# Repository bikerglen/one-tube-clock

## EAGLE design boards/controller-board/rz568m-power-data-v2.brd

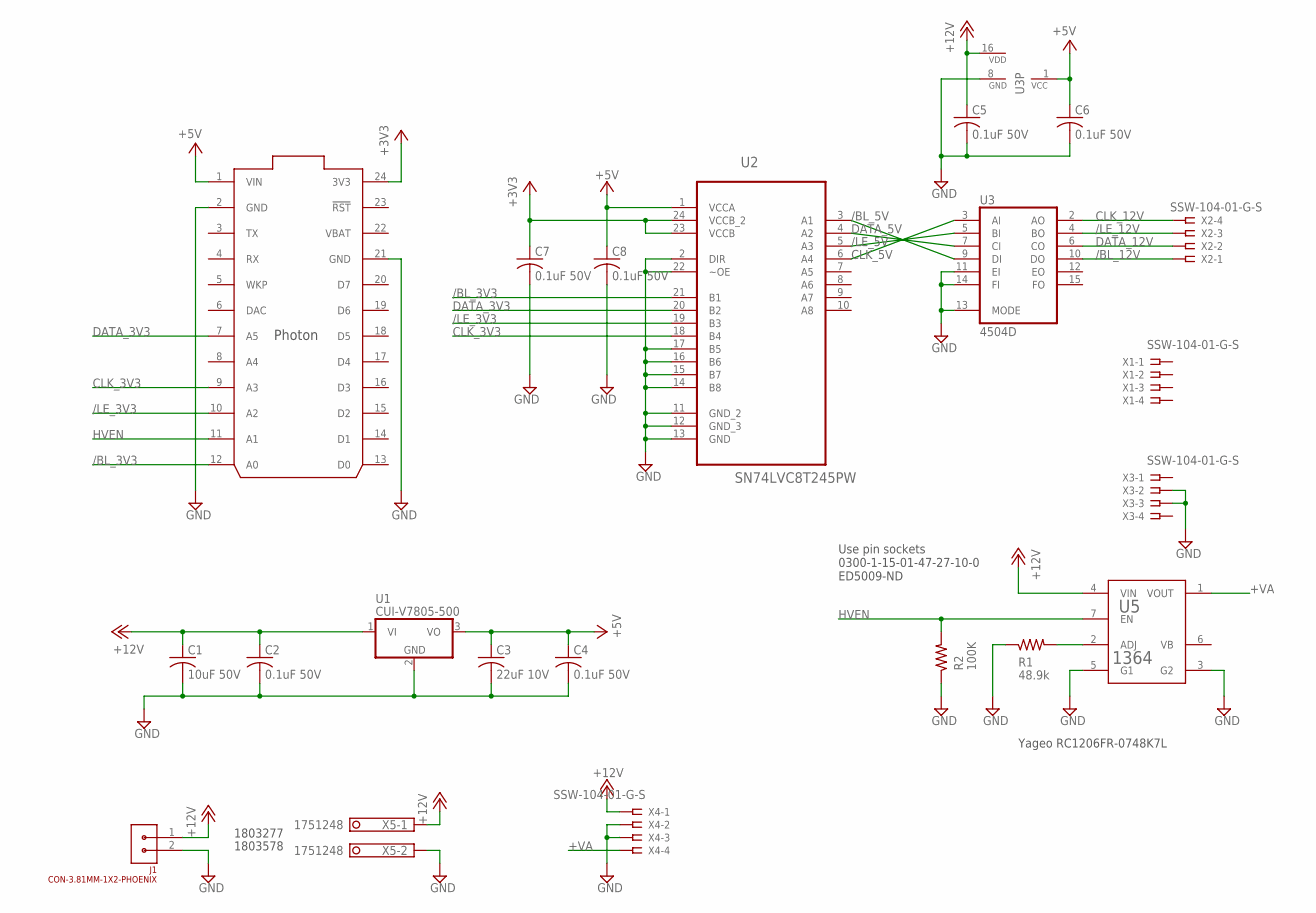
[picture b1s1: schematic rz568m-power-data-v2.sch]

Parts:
C1: 10uF 50V; C1210K; MFR_PART_NO C1210C106K5RACTU
C2, C4: 0.1uF 50V; C1206K; MFR_PART_NO C1206S104M5RACTU
C3: 22uF 10V; C1206K; MFR_PART_NO C1206C226K8RAC7800
C5, C6, C7, C8: 0.1uF 50V; C0805K; MFR_PART_NO C1206S104M5RACTU
J1: CON-3.81MM-1X2-PHOENIX; CON-PHOENIX-3.81-1X2-RA
R1: 48.9k; R1206
R2: 100K; R1206
U1: CUI-V7805-500; CUI-78XX-500
U2: SN74LVC8T245PW; SOP65P640X120-24N
U3: 4504D; SO16
U4: PHOTON_WITH_HEADERS; PHOTON
U5: 1364
X1, X2, X3, X4: SSW-104-01-G-S; SSW-104-02-S-S
X5: 1751248

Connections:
+3V3: C7.1, U2.23 (VCCB), U2.24 (VCCB_2), U4.24 (3V3)
+5V: C3.1, C4.1, C6.1, C8.1, U1.3 (VO), U2.1 (VCCA), U3.1 (VCC), U4.1 (VIN)
+12V: C1.1, C2.1, C5.1, J1.1, U1.1 (VI), U3.16 (VDD), U5.4 (VIN), X4.1, X5.1
+VA: U5.1 (VOUT), X4.4
/BL_3V3: U2.21 (B1), U4.12 (A0)
/BL_5V: U2.3 (A1), U3.9 (DI)
/BL_12V: U3.10 (DO), X2.1
/LE_3V3: U2.19 (B3), U4.10 (A2)
/LE_5V: U2.5 (A3), U3.5 (BI)
/LE_12V: U3.4 (BO), X2.3
CLK_3V3: U2.18 (B4), U4.9 (A3)
CLK_5V: U2.6 (A4), U3.3 (AI)
CLK_12V: U3.2 (AO), X2.4
DATA_3V3: U2.20 (B2), U4.7 (A5)
DATA_5V: U2.4 (A2), U3.7 (CI)
DATA_12V: U3.6 (CO), X2.2
GND: C1.2, C2.2, C3.2, C4.2, C5.2, C6.2, C7.2, C8.2, J1.2, R1.1, R2.1, U1.2 (GND), U2.2 (DIR), U2.11 (GND_2), U2.12 (GND_3), U2.13 (GND), U2.14 (B8), U2.15 (B7), U2.16 (B6), U2.17 (B5), U2.22 (~OE), U3.8 (GND), U3.11 (EI), U3.13 (MODE), U3.14 (FI), U4.2 (GND), U4.21 (GND), U5.3 (G2), U5.5 (G1), X3.2, X3.3, X4.2, X4.3, X5.2
HVEN: R2.2, U4.11 (A1), U5.7 (EN)
unnamed: R1.2, U5.2 (ADJ)
VBAT: U4.22 (VBAT)

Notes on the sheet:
Yageo RC1206FR-0748K7L
1803277
1803578
Use pin sockets 0300-1-15-01-47-27-10-0 ED5009-ND

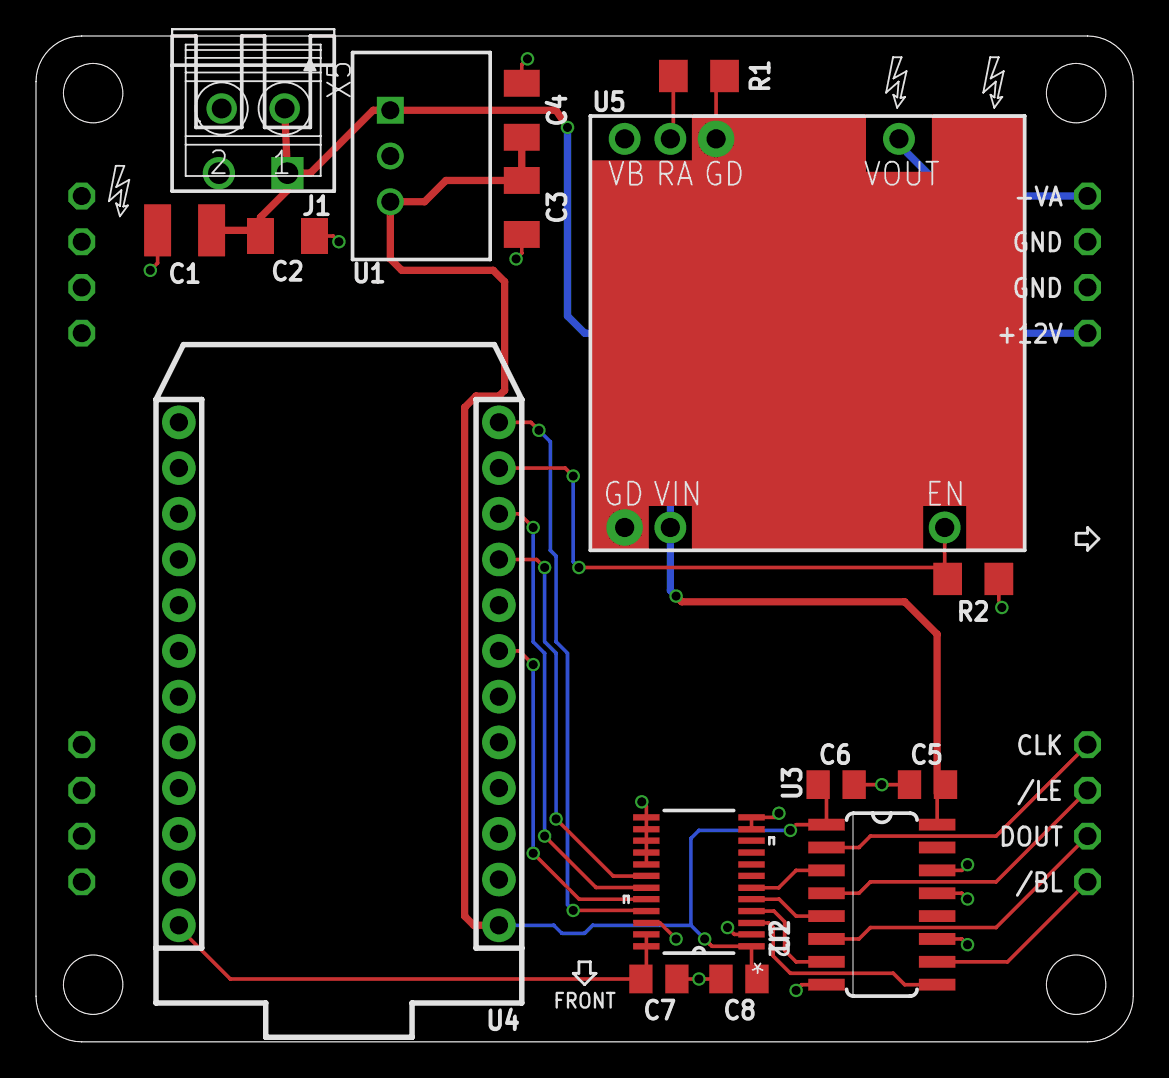
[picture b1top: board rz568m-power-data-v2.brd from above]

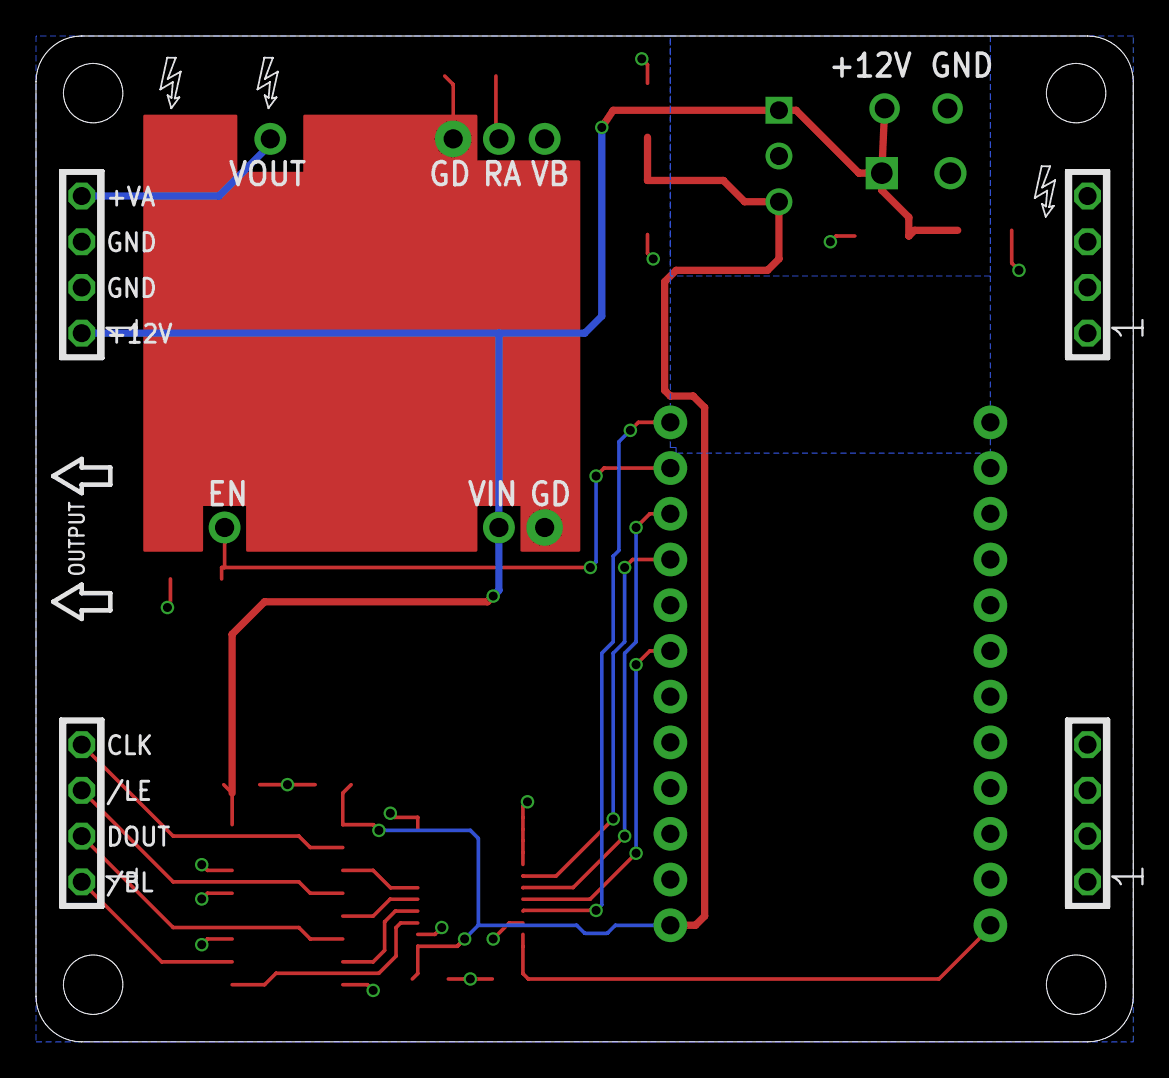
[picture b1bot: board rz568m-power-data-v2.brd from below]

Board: 2 copper layers, 61.0 x 55.9 mm, 21 parts (4 on the bottom side), 19 nets.

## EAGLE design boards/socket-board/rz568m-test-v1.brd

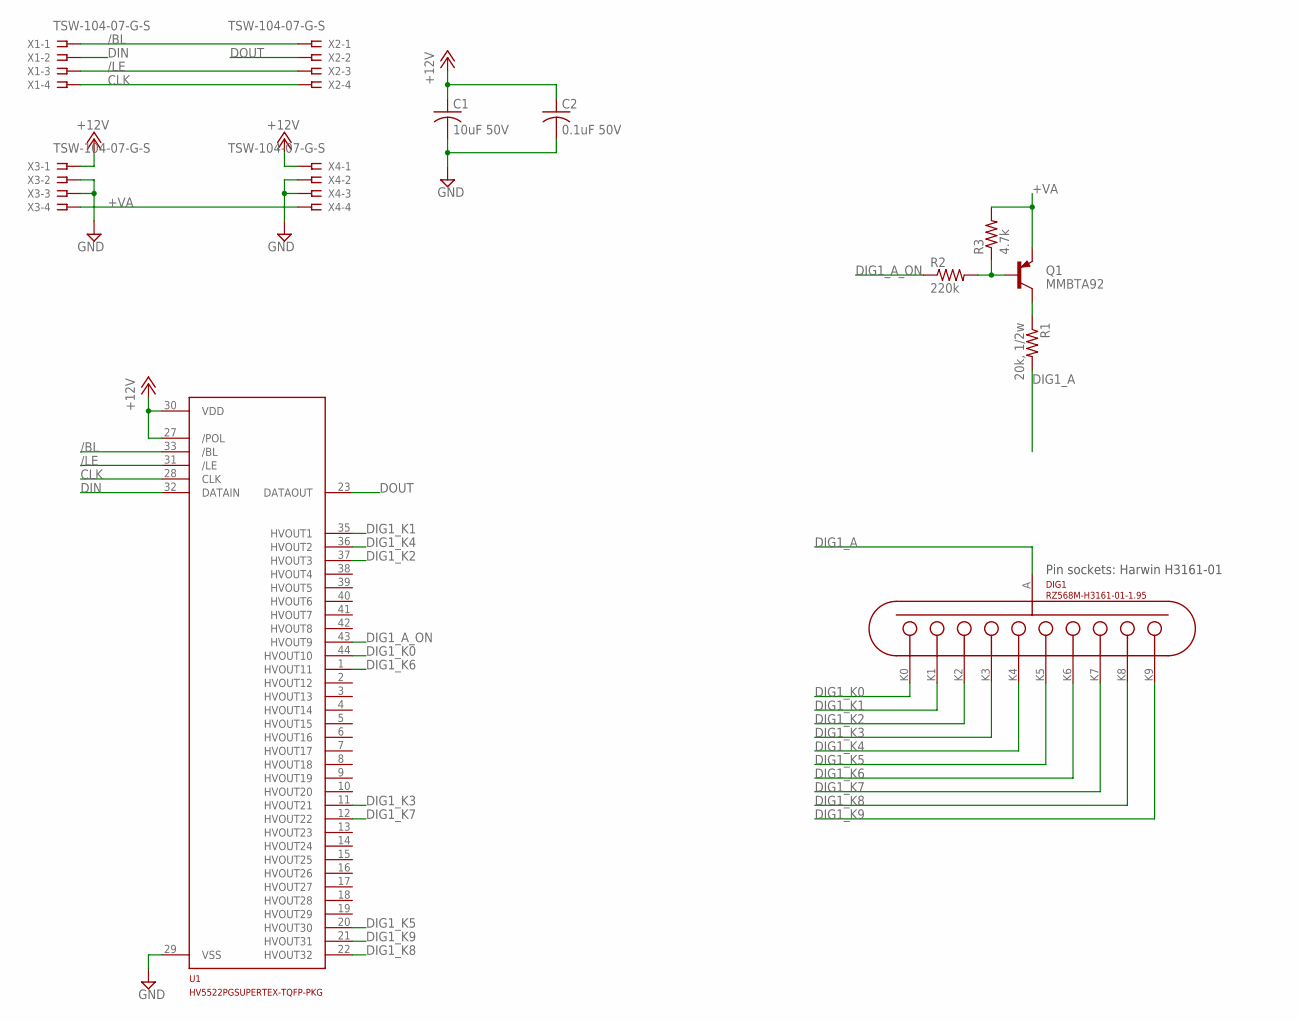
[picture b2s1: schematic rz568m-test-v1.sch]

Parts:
C1: 10uF 50V; C1210K; MFR_PART_NO C1210C106K5RACTU
C2: 0.1uF 50V; C1206K; MFR_PART_NO C1206S104M5RACTU
DIG1: RZ568M-H3161-01-1.95; MFR_PART_NO H3161-01
Q1: MMBTA92; SOT23-BEC; MFR_PART_NO MMBTA92
R1: 20k, 1/2w; R1210; MFR_PART_NO ERJ-14NF2002U
R2: 220k; R1206; MFR_PART_NO ERJ-8GEYJ224V
R3: 4.7k; R1206; MFR_PART_NO ERJ-8ENF4701V
U1: HV5522PGSUPERTEX-TQFP-PKG; TQFP44-HV5522PG; MFR_PART_NO HV5522PG
X1, X2, X3, X4: TSW-104-07-G-S; SSW-104-02-S-S; MFR_PART_NO TSW-104-07-G-S

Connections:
+12V: C1.1, C2.1, U1.27 (/POL), U1.30 (VDD), X3.1, X4.1
+VA: Q1.E, R3.2, X3.4, X4.4
/BL: U1.33 (/BL), X1.1, X2.1
/LE: U1.31 (/LE), X1.3, X2.3
CLK: U1.28 (CLK), X1.4, X2.4
DIG1_A: DIG1.A, R1.2
DIG1_A_ON: R2.1, U1.43 (HVOUT9)
DIG1_BASE: Q1.B, R2.2, R3.1
DIG1_COLLECTOR: Q1.C, R1.1
DIG1_K0: DIG1.K0, U1.44 (HVOUT10)
DIG1_K1: DIG1.K1, U1.35 (HVOUT1)
DIG1_K2: DIG1.K2, U1.37 (HVOUT3)
DIG1_K3: DIG1.K3, U1.11 (HVOUT21)
DIG1_K4: DIG1.K4, U1.36 (HVOUT2)
DIG1_K5: DIG1.K5, U1.20 (HVOUT30)
DIG1_K6: DIG1.K6, U1.1 (HVOUT11)
DIG1_K7: DIG1.K7, U1.12 (HVOUT22)
DIG1_K8: DIG1.K8, U1.22 (HVOUT32)
DIG1_K9: DIG1.K9, U1.21 (HVOUT31)
DIN: U1.32 (DATAIN), X1.2
DOUT: U1.23 (DATAOUT), X2.2
GND: C1.2, C2.2, U1.29 (VSS), X3.2, X3.3, X4.2, X4.3

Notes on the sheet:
Pin sockets: Harwin H3161-01

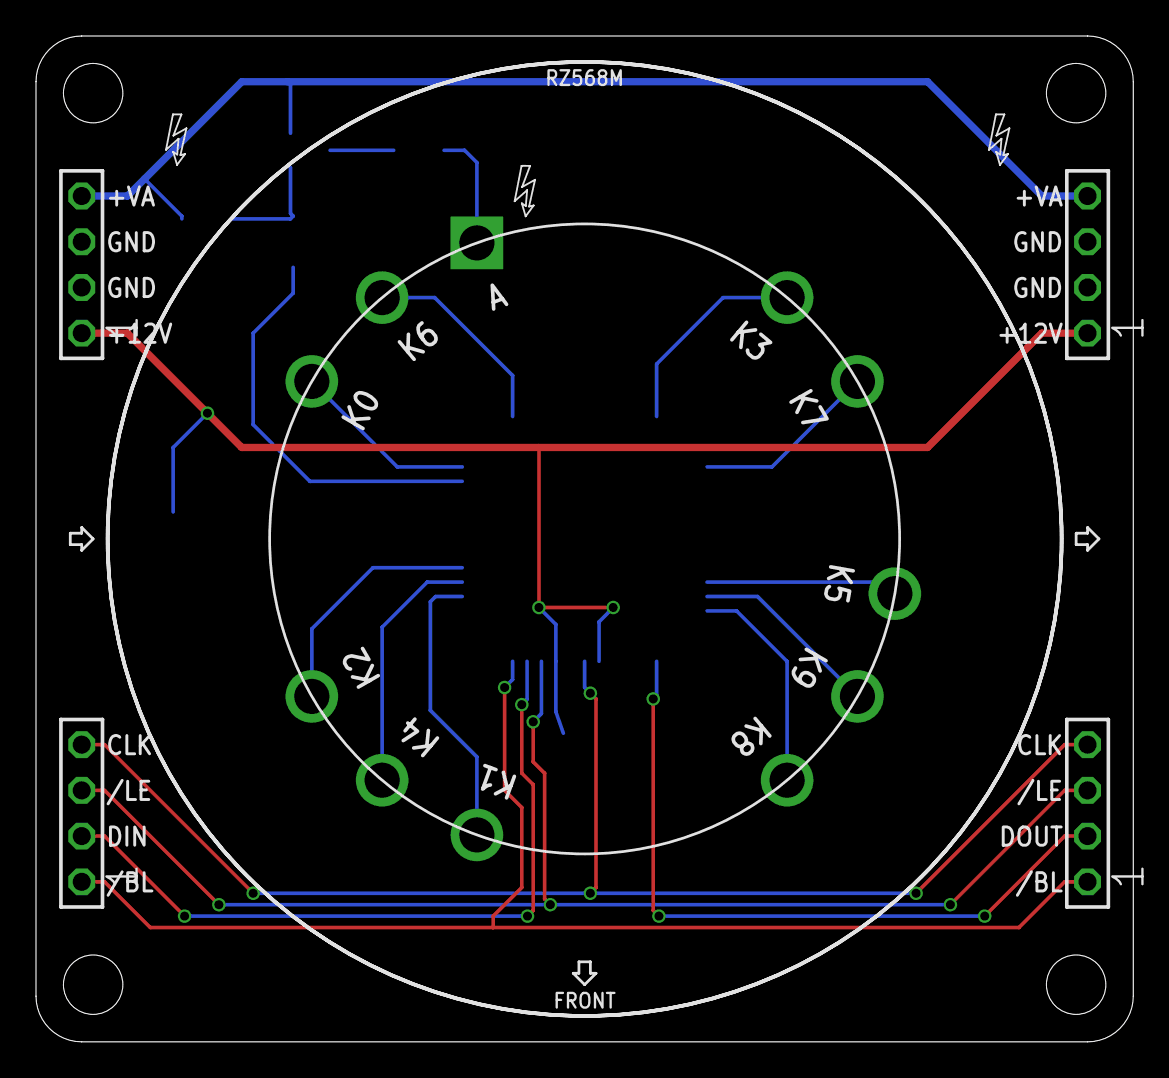
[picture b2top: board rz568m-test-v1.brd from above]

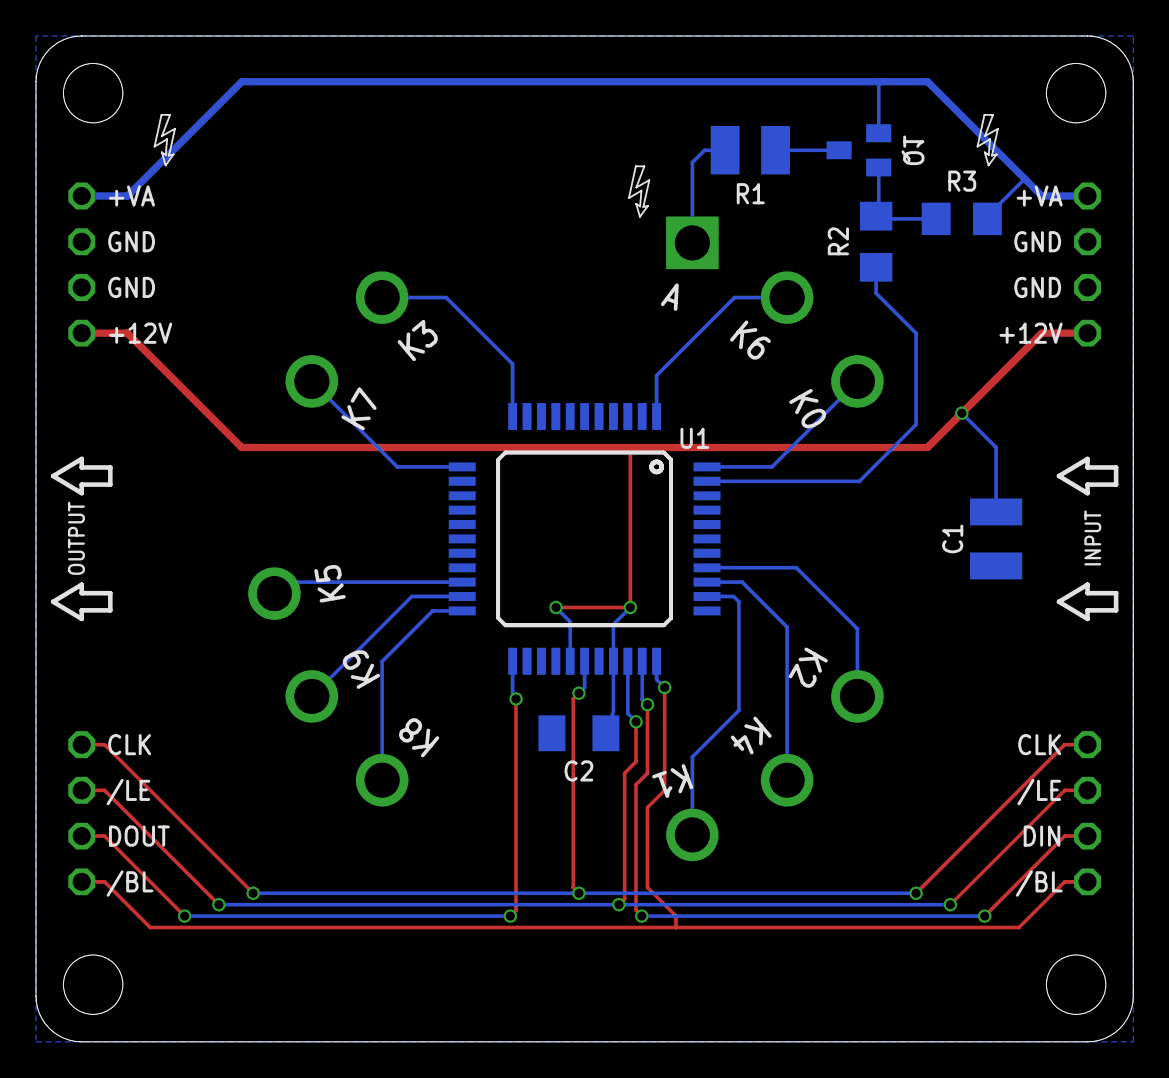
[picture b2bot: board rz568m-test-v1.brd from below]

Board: 2 copper layers, 61.0 x 55.9 mm, 12 parts (7 on the bottom side), 22 nets.

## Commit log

2020-06-04 initial checkin of boards
